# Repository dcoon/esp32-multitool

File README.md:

# ESP32 Multitool

ESP32 Multitool is an I/O board for ESP32 microcontroller based projects.  It is designed for IoT projects on a boat but can be used in automotive, RV, and home environments.  It is designed to be inexpensive, robust, energy efficient, and easy to use.  It supports firmware from multiple open source projects including ESPHome, ESPSense, and Platformio.

## Features

- 3x Analog Inputs
	- +0-30VDC
	- Measure voltage or resistance
- 3x PWM/Switch Outputs
	- Configurable voltage from VIN, +5V, and External
	- 1A current per channel
- 1x Pulse/Tachometer Input
- 1x Digital Potentiometer
- CAN/N2K 
- RS422/NMEA 0183
- 1-Wire
- I2C
	- Qwiic and Adafruit compatible I2C connector
- SPI
- Wifi/BLE
- Power
	- +5 - 30VDC Input
	- OVP, RV, and ESD Protection
- Software Compatibility
	- ESPHome
	- ESPSense
	- Platformio

## Examples

TBD

### Tank Level Monitor
### Engine Monitor
### Fan Controller
### LED Dimmer

### More
- Refridgerator Controller
- Barometer & Lightning Detector

## Acknowledgements

### Sailorhat

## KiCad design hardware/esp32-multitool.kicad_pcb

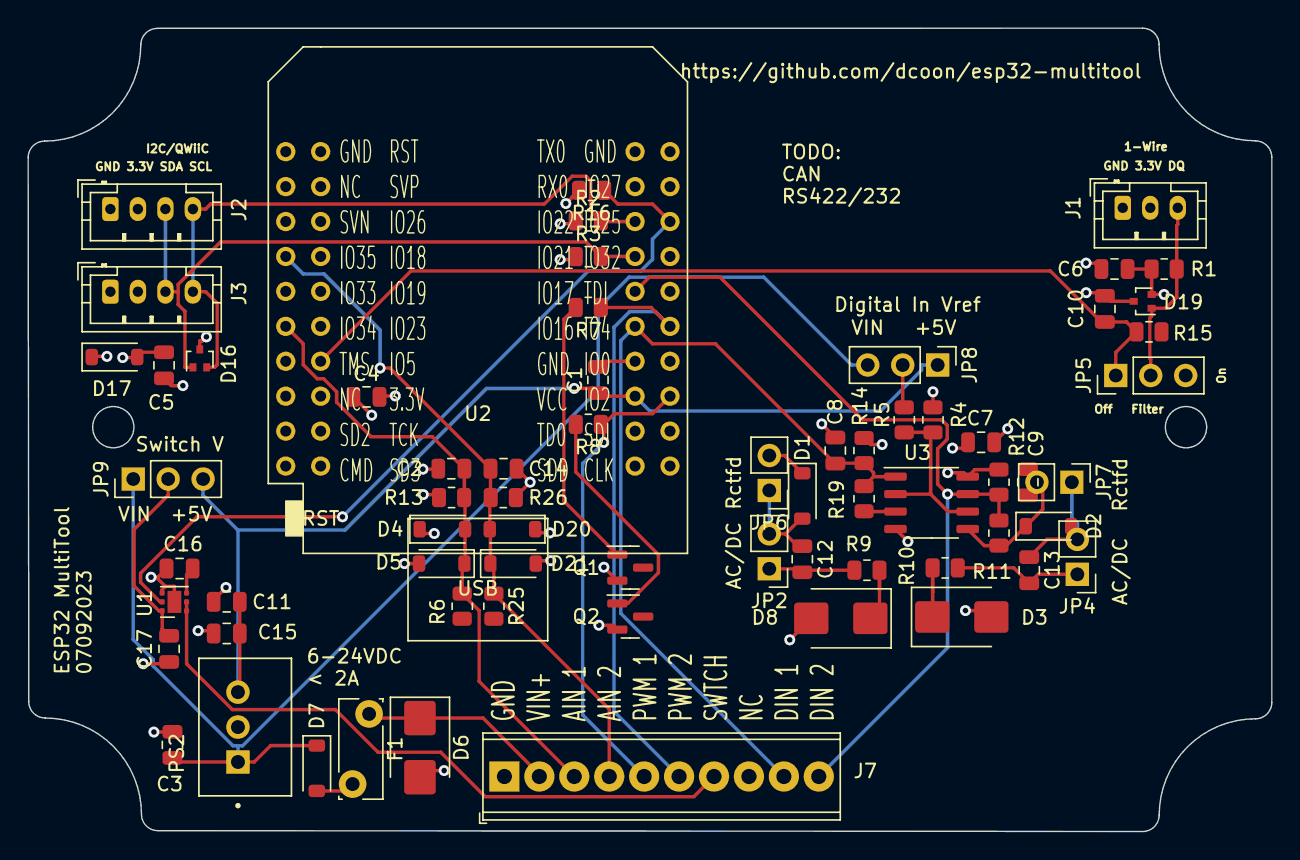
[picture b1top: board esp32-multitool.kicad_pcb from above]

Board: 4 copper layers, 90.4 x 58.4 mm, 67 parts (0 on the bottom side), 32 nets.

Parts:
C1, C2, C4, C5, C6, C7, C8, C9, C14: 1uF; C_0805_2012Metric
C3: 10uF/50V; C_0805_2012Metric
C10: 1nF; C_0805_2012Metric
C11, C15: 47uF/16V; C_0805_2012Metric
C12, C13: 22nF/30V; C_0805_2012Metric
C16: 4700p; C_0805_2012Metric
C17: 4.7uF/30V; C_0805_2012Metric
D1, D2, D4, D5, D7, D20, D21: D_SCHOTTKY_30V; D_SOD-123
D3, D6, D8: D_TVS_30V; D_SMB
D16, D19: RCLAMP0502B; SOT-416
D17: D_TVS_3V3; D_SOD-123
F1: Fuse; Fuse_Bourns_MF-RG300
J1: Conn_01x03/1Wire; JST_PH_B3B-PH-K_1x03_P2.00mm_Vertical
J2, J3: Conn_01x04/QWiiC; JST_PH_B4B-PH-K_1x04_P2.00mm_Vertical
J7: Conn_01x09; TerminalBlock_Phoenix_MPT-0,5-10-2.54_1x10_P2.54mm_Horizont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
JP2, JP4, JP6, JP7: Jumper_2_Bridged; PinHeader_1x02_P2.54mm_Vertical
JP5, JP9: Jumper_3_Bridged12; PinHeader_1x03_P2.54mm_Vertical
JP8: Jumper_2_Open; PinHeader_1x03_P2.54mm_Vertical
PS2: TPSM84205EAB
Q1, Q2: AO3400A; SOT-23
R1: 4.7k; R_0805_2012Metric
R2, R3: 2.7k; R_0805_2012Metric
R4, R5: 10k; R_0805_2012Metric
R6, R9, R10, R25: 100k; R_0805_2012Metric
R7, R8: 100; R_0805_2012Metric
R11, R13, R19, R26: 1M; R_0805_2012Metric
R12, R14: 5.1K; R_0805_2012Metric
R15: 150; R_0805_2012Metric
R16: 10k/30V; R_0805_2012Metric
U1: TPS22810DRV; WSON-6-1EP_2x2mm_P0.65mm_EP1x1.6mm
U2: wemos_mini_esp32; ESP32_mini
U3: LM393; SOP-8_3.9x4.9mm_P1.27mm

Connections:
+3.3V: C4.1, C5.1, C6.1, C7.1, D4.1 (K), D17.2 (A2), D19.2 (K2), D20.1 (K), J1.2, J2.2, J3.2, R1.2, R2.1, R3.1, R12.1, R14.1, U2.16 (3V3), U3.8 (V+)
+5V: C1.1, C11.1, C15.1, JP8.1 (A), JP9.3 (B), PS2.3 (VOUT), U2.35 (VCC_(USB))
/1WIRE_DQ: C10.1, JP5.1 (A), R15.1, U2.14 (IO_05/D8)
/1wire/DQ: D19.1 (K1), J1.3, JP5.2 (C), R1.1
/AIN1: C2.1, D4.2 (A), D5.1 (K), J7.3, R6.1, R13.1, U2.11 (IO_34)
/AIN2: C14.1, D20.2 (A), D21.1 (K), J7.4, R25.1, R26.1, U2.7 (IO_35)
/DIN1: C8.1, J7.9, R14.2, R19.2, U2.31 (IO_16/D4), U3.1
/DIN2: C9.1, J7.10, R11.2, R12.2, U2.29 (IO_17/D3), U3.7
/DIN_LINE1: D8.1 (A1), R9.2
/DIN_LINE2: D3.1 (A1), R10.2
/I2C_SCL: D16.2 (K2), J2.4, J3.4, R2.2, U2.25 (IO_22/D1/SCL)
/I2C_SDA: D16.1 (K1), J2.3, J3.3, R3.2, U2.27 (IO_21/D2/SDA)
/PWM1: J7.5, R8.1, U2.36 (IO_02)
/PWM2: J7.6, R7.1, U2.32 (IO_04)
/SWITCH1: R16.1, U1.5 (EN/UVLO), U2.26 (IO_25)
/SWITCH_LINE1: J7.7, U1.1 (VOUT), U1.2 (QOD)
/VIN: D6.1 (A1), F1.1, J7.2
/digital_in/DIN_VREF: R4.2, R5.1, U3.2 (-), U3.6 (-)
GND: C1.2, C2.2, C3.2, C4.2, C5.2, C6.2, C7.2, C8.2, C9.2, C10.2, C11.2, C14.2, C15.2, C16.2, C17.2, D3.2 (A2), D5.2 (A), D6.2 (A2), D8.2 (A2), D16.3 (A), D17.1 (A1), D19.3 (A), D21.2 (A), J1.1, J2.1, J3.1, J7.1, PS2.2 (GND), Q1.2 (S), Q2.2 (S), R5.2, R13.2, R16.2, R26.2, U1.4 (GND), U1.7 (GND), U2.1 (GND), U2.22 (GND), U2.33 (GND), U3.4 (V-)
unnamed: C12.1, D1.2 (A), JP2.2 (B), JP6.1 (A)
unnamed: D1.1 (K), JP6.2 (B), R19.1, U3.3 (+)
unnamed: C13.1, D2.2 (A), JP4.2 (B), JP7.1 (A)
unnamed: D2.1 (K), JP7.2 (B), R11.1, U3.5 (+)
unnamed: D7.2 (A), F1.2
unnamed: C12.2, JP2.1 (A), R9.1
unnamed: C13.2, JP4.1 (A), R10.1
unnamed: JP8.2 (C), R4.1
unnamed: C17.1, JP9.2 (C), U1.6 (VIN)
unnamed: Q1.1 (G), R7.2
unnamed: Q2.1 (G), R8.2
unnamed: C16.1, U1.3 (CT)
VPP: C3.1, D7.1 (K), JP8.3 (B), JP9.1 (A), PS2.1 (VIN)

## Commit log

2022-09-04 Initial schematic and board layout
2022-09-04 First draft of README
2022-09-04 Added obsidian prefs to gitignore
2023-06-14 renamed multitool to hardware
2023-07-04 block refactoring
2023-07-08 moving subsheets to blocks
2023-07-12 Added 3D models and ran freerouting

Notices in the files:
hardware/esp32-multitool.kicad_pcb:
https://creativecommons.org/licenses/by-sa/4.0
SH-ESP32 is licensed under CC BY-SA 4.0.
